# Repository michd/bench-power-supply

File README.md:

# Bench power supply

I'm working (currently just researching and prototyping) on developing my own bench power supply. This repository will mostly act as a working directory before it gets anywhere near completion, so expect stuff to move around a lot.

## Some requirements / desired features for the supply:

- DC output voltage of 1.5V - 35V (ish)
- Output current of up to 2.5~3A (ish)
- Voltage and current limit digitally adjustable, probably through rotary encoders
- Present output voltage and current displayed on LED 7 segment displays
- Additional (LCD?) display for setting the voltage and current limit (definitely need a way to view the current limit when it's not being reached)
- Maybe some USB ports (3?) providing 5V / 1A per port.

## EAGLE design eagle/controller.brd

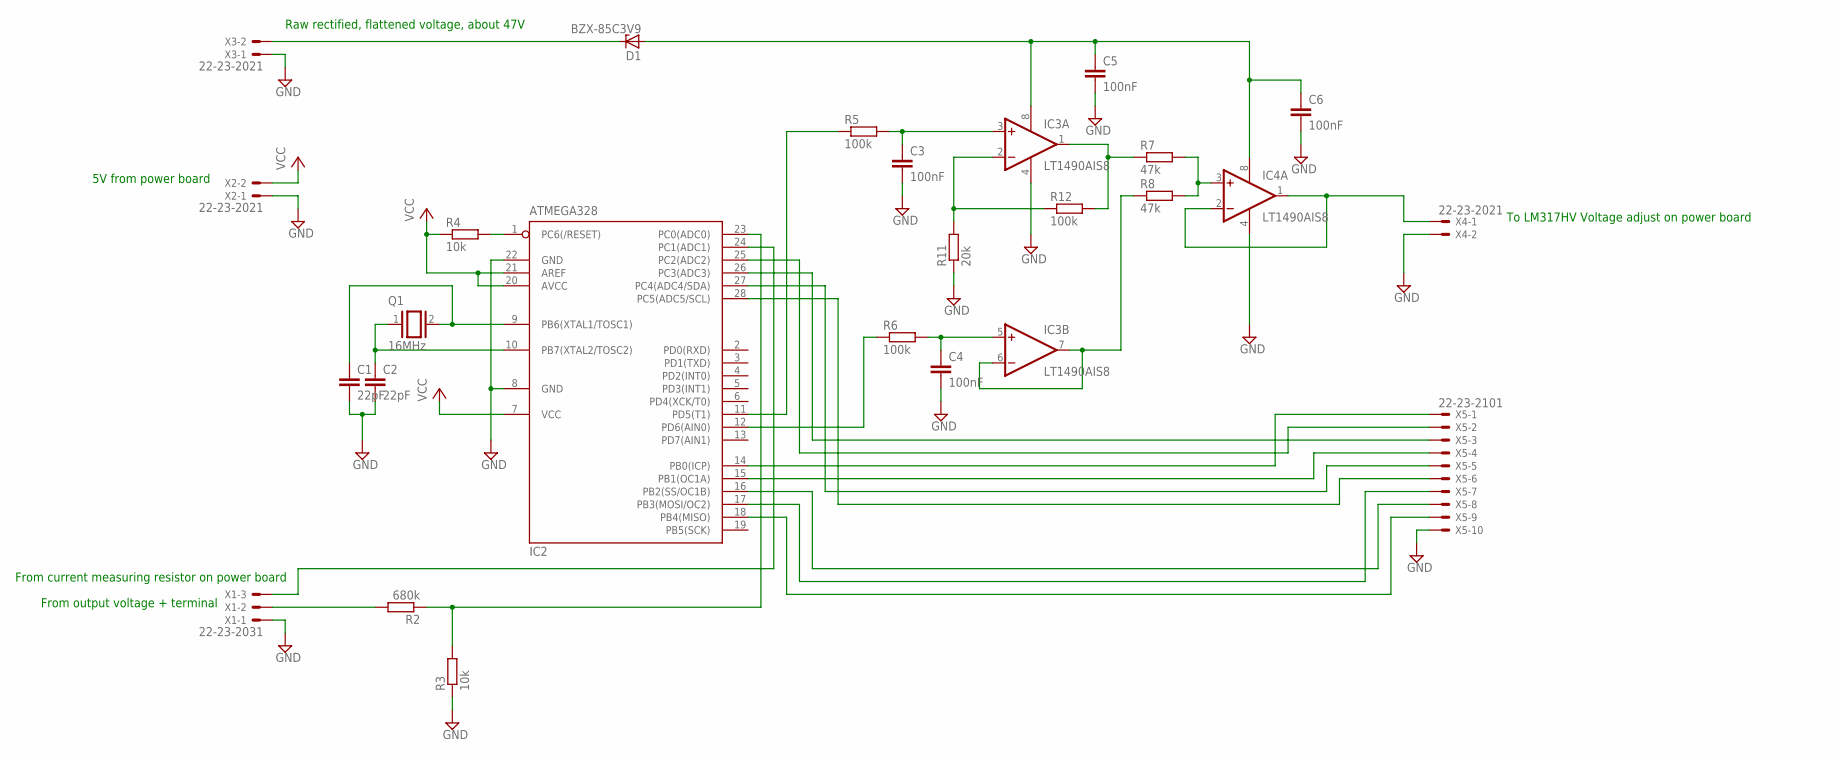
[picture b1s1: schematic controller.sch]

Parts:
C1, C2: 22pF; C2.5-2
C3, C4, C5, C6: 100nF; C7.5B3
D1: BZX-85C3V9; DO34Z7
IC2: ATMEGA328; DIL28-3
IC3, IC4: LT1490AIS8; SO08
Q1: 16MHz; QS
R2: 680k; 0207/10
R3, R4: 10k; 0207/10
R5, R6, R12: 100k; 0207/10
R7, R8: 47k; 0207/10
R11: 20k; 0207/10
X1: 22-23-2031
X2, X3, X4: 22-23-2021
X5: 22-23-2101

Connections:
GND: C1.2, C2.2, C3.2, C4.2, C5.2, C6.2, IC2.8 (GND), IC2.22 (GND), IC3.4 (V-), IC4.4 (V-), R3.1, R11.1, X1.1, X2.1, X3.1, X4.2, X5.10
unnamed: IC2.18 (PB4(MISO)), X5.9
unnamed: IC2.16 (PB2(SS/OC1B)), X5.8
unnamed: IC2.17 (PB3(MOSI/OC2)), X5.7
unnamed: IC2.7 (VCC), IC2.20 (AVCC), IC2.21 (AREF), R4.1, X2.2
unnamed: IC3.1 (OUT), R7.1, R12.2
unnamed: IC2.14 (PB0(ICP)), X5.1
unnamed: IC2.24 (PC1(ADC1)), X1.3
unnamed: IC2.23 (PC0(ADC0)), R2.1, R3.2
unnamed: R2.2, X1.2
unnamed: C1.1, IC2.9 (PB6(XTAL1/TOSC1)), Q1.2
unnamed: C2.1, IC2.10 (PB7(XTAL2/TOSC2)), Q1.1
unnamed: IC3.6 (-IN), IC3.7 (OUT), R8.1
unnamed: IC2.11 (PD5(T1)), R5.1
unnamed: IC2.1 (PC6(/RESET)), R4.2
unnamed: C3.1, IC3.3 (+IN), R5.2
unnamed: C4.1, IC3.5 (+IN), R6.2
unnamed: C5.1, C6.1, D1.A, IC3.8 (V+), IC4.8 (V+)
unnamed: IC2.12 (PD6(AIN0)), R6.1
unnamed: IC4.3 (+IN), R7.2, R8.2
unnamed: IC3.2 (-IN), R11.2, R12.1
unnamed: IC4.1 (OUT), IC4.2 (-IN), X4.1
unnamed: IC2.15 (PB1(OC1A)), X5.4
unnamed: IC2.25 (PC2(ADC2)), X5.2
unnamed: IC2.28 (PC5(ADC5/SCL)), X5.6
unnamed: IC2.27 (PC4(ADC4/SDA)), X5.5
unnamed: D1.C, X3.2
unnamed: IC2.26 (PC3(ADC3)), X5.3

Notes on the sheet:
5V from power board
Raw rectified, flattened voltage, about 47V
To LM317HV Voltage adjust on power board
From current measuring resistor on power board
From output voltage + terminal

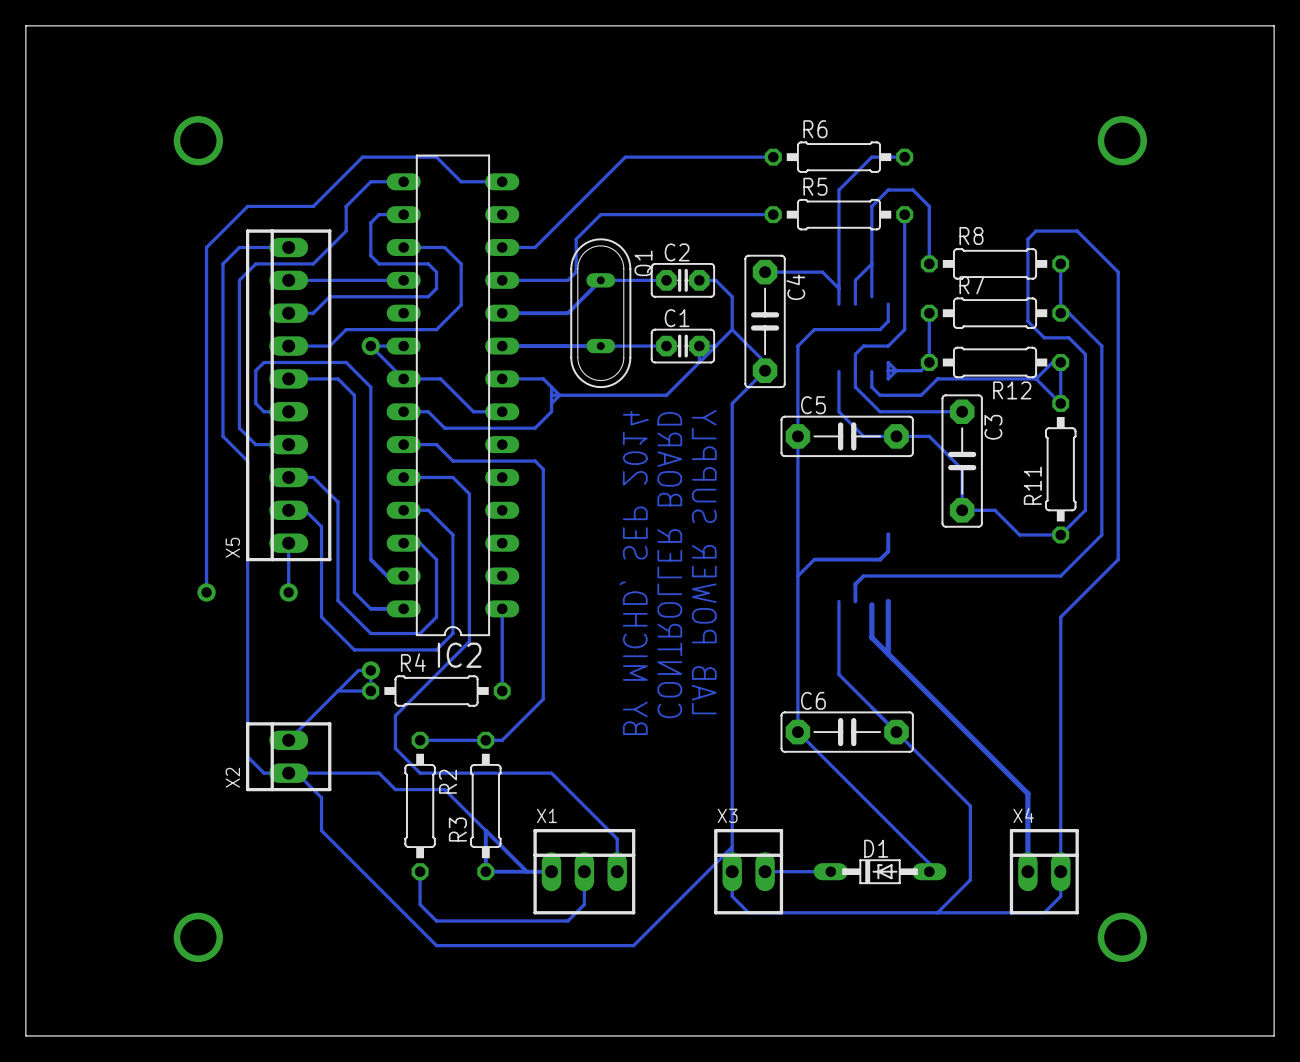
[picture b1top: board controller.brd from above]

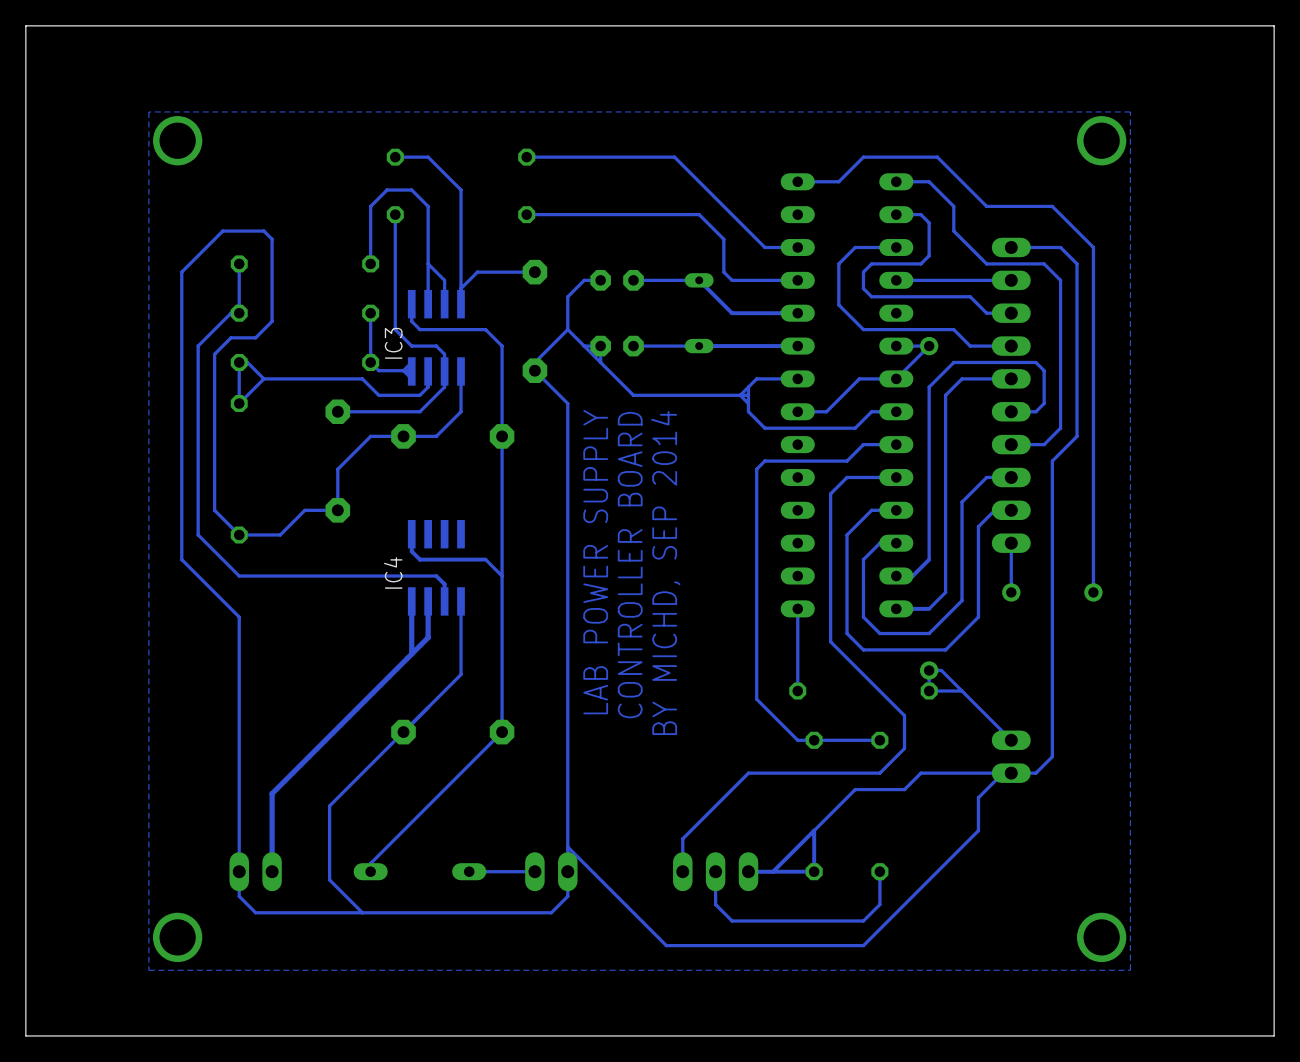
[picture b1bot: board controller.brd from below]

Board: 2 copper layers, 96.5 x 78.1 mm, 25 parts (2 on the bottom side), 28 nets.

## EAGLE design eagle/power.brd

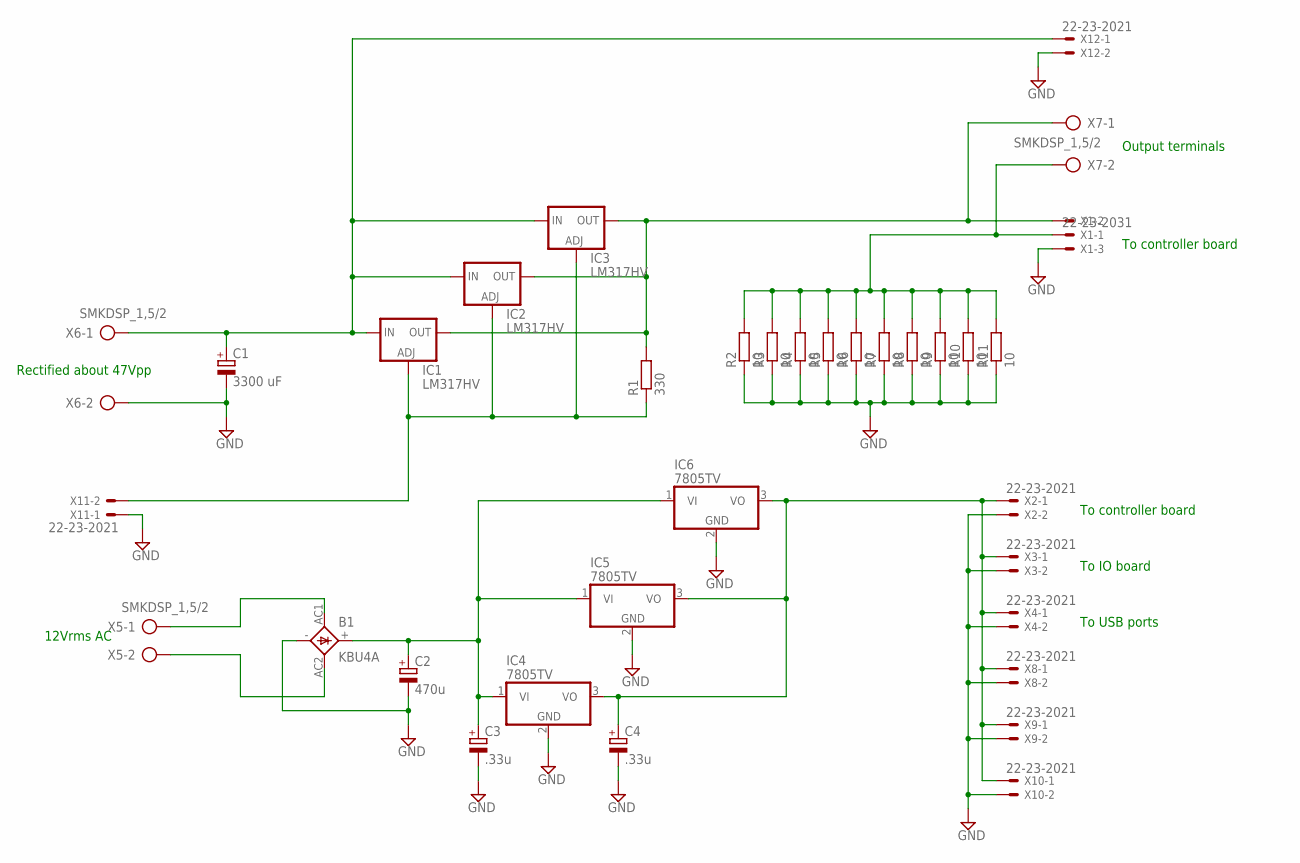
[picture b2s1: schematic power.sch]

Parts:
B1: KBU4A; 2KBB-R
C1: 3300 uF; EB25D
C2: 470u; E5-10,5
C3, C4: .33u; E2-5
IC1, IC2, IC3: LM317HV; 317TS
IC4, IC5, IC6: 7805TV; TO220V
R1: 330; 0207/7
R2, R3, R4, R5, R6, R7, R8, R9, R10, R11: 10; 0204/7
X1: 22-23-2031
X2, X3, X4, X8, X9, X10, X11, X12: 22-23-2021
X5, X6, X7: SMKDSP_1,5/2

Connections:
GND: B1.-, C1.-, C2.-, C3.-, C4.-, IC4.2 (GND), IC5.2 (GND), IC6.2 (GND), R2.1, R3.1, R4.1, R5.1, R6.1, R7.1, R8.1, R9.1, R10.1, R11.1, X1.3, X2.2, X3.2, X4.2, X6.2, X8.2, X9.2, X10.2, X11.1, X12.2
unnamed: B1.AC1, X5.1
unnamed: C1.+, IC1.3 (IN), IC2.3 (IN), IC3.3 (IN), X6.1, X12.1
unnamed: B1.AC2, X5.2
unnamed: IC1.2 (OUT), IC2.2 (OUT), IC3.2 (OUT), R1.2, X1.2, X7.1
unnamed: B1.+, C2.+, C3.+, IC4.1 (VI), IC5.1 (VI), IC6.1 (VI)
unnamed: C4.+, IC4.3 (VO), IC5.3 (VO), IC6.3 (VO), X2.1, X3.1, X4.1, X8.1, X9.1, X10.1
unnamed: IC1.1 (ADJ), IC2.1 (ADJ), IC3.1 (ADJ), R1.1, X11.2
unnamed: R2.2, R3.2, R4.2, R5.2, R6.2, R7.2, R8.2, R9.2, R10.2, R11.2, X1.1, X7.2

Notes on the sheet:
Rectified about 47Vpp
12Vrms AC
Output terminals
To controller board
To IO board
To USB ports

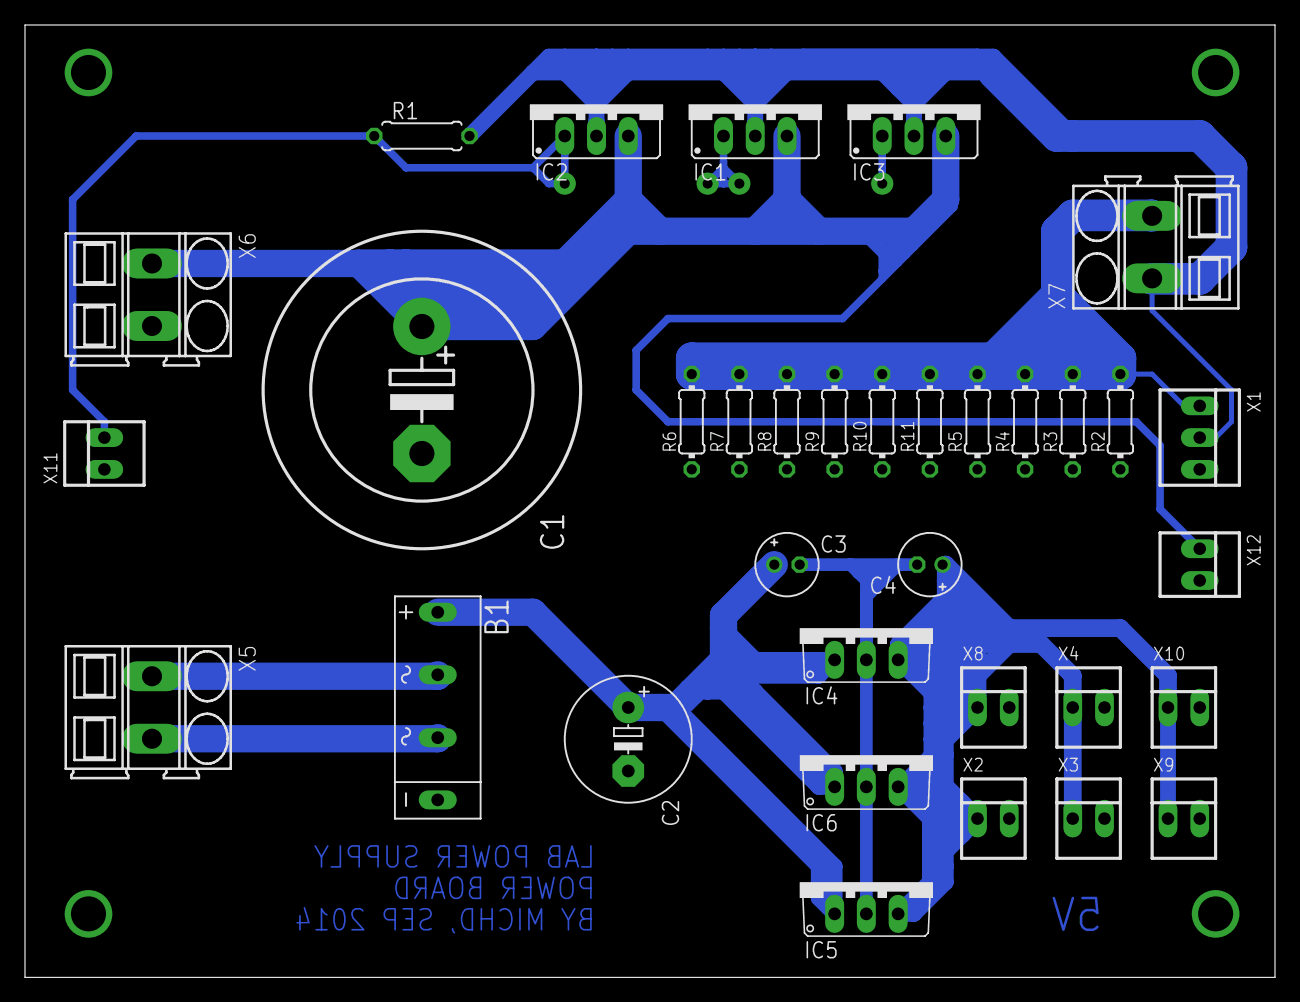
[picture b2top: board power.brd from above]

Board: 2 copper layers, 100.0 x 76.2 mm, 34 parts (0 on the bottom side), 9 nets.

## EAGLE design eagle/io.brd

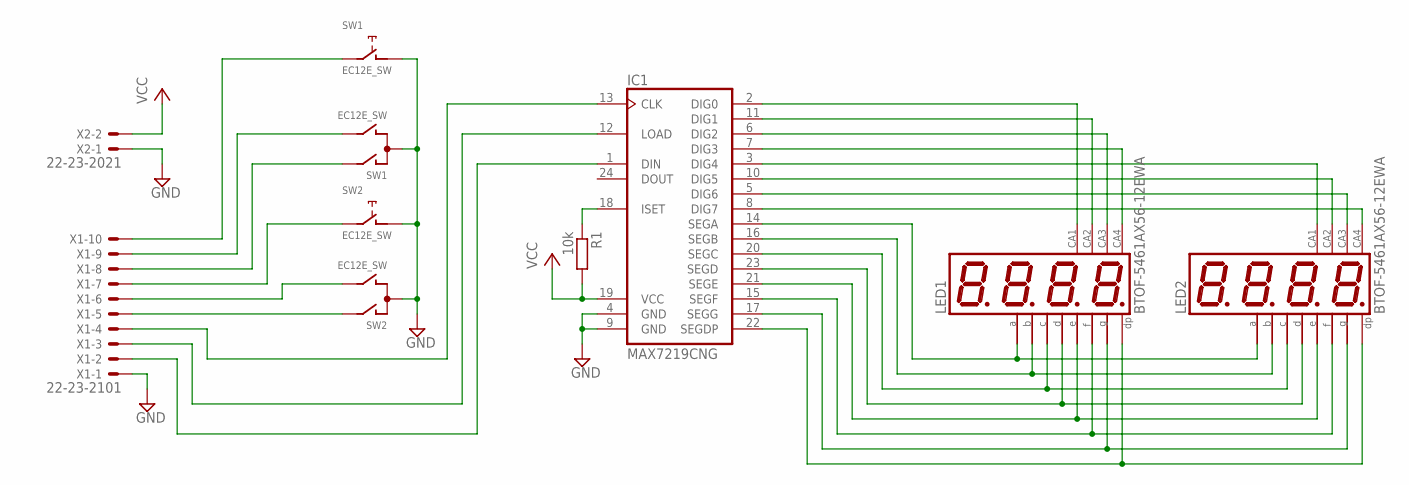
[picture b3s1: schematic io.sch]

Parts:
IC1: MAX7219CNG; DIL24-3
LED1, LED2: BTOF-5461AX56-12EWA; BX56-12
R1: 10k; 0207/10
SW1, SW2: EC12E_SW; ALPS_EC12E_SW
X1: 22-23-2101
X2: 22-23-2021

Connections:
GND: IC1.4 (GND), IC1.9 (GND), SW1.C, SW1.D (1), SW2.C, SW2.D (1), X1.1, X2.1
unnamed: IC1.12 (LOAD), X1.3
unnamed: IC1.2 (DIG0), LED1.12 (CA)
unnamed: IC1.11 (DIG1), LED1.9 (CA)
unnamed: IC1.6 (DIG2), LED1.8 (CA)
unnamed: IC1.3 (DIG4), LED2.12 (CA)
unnamed: IC1.5 (DIG6), LED2.8 (CA)
unnamed: IC1.8 (DIG7), LED2.6 (CA)
unnamed: IC1.16 (SEGB), LED1.7 (B), LED2.7 (B)
unnamed: IC1.20 (SEGC), LED1.4 (C), LED2.4 (C)
unnamed: IC1.23 (SEGD), LED1.2 (D), LED2.2 (D)
unnamed: IC1.21 (SEGE), LED1.1 (E), LED2.1 (E)
unnamed: IC1.15 (SEGF), LED1.10 (F), LED2.10 (F)
unnamed: IC1.13 (CLK), X1.4
unnamed: IC1.18 (ISET), R1.1
unnamed: IC1.17 (SEGG), LED1.5 (G), LED2.5 (G)
unnamed: IC1.22 (SEGDP), LED1.3 (DP), LED2.3 (DP)
unnamed: IC1.1 (DIN), X1.2
unnamed: IC1.14 (SEGA), LED1.11 (A), LED2.11 (A)
unnamed: IC1.10 (DIG5), LED2.9 (CA)
unnamed: SW2.E (2), X1.7
unnamed: SW1.E (2), X1.10
unnamed: SW1.B, X1.9
unnamed: SW2.A, X1.5
unnamed: SW2.B, X1.6
unnamed: SW1.A, X1.8
unnamed: IC1.7 (DIG3), LED1.6 (CA)
VCC: IC1.19 (VCC), R1.2, X2.2

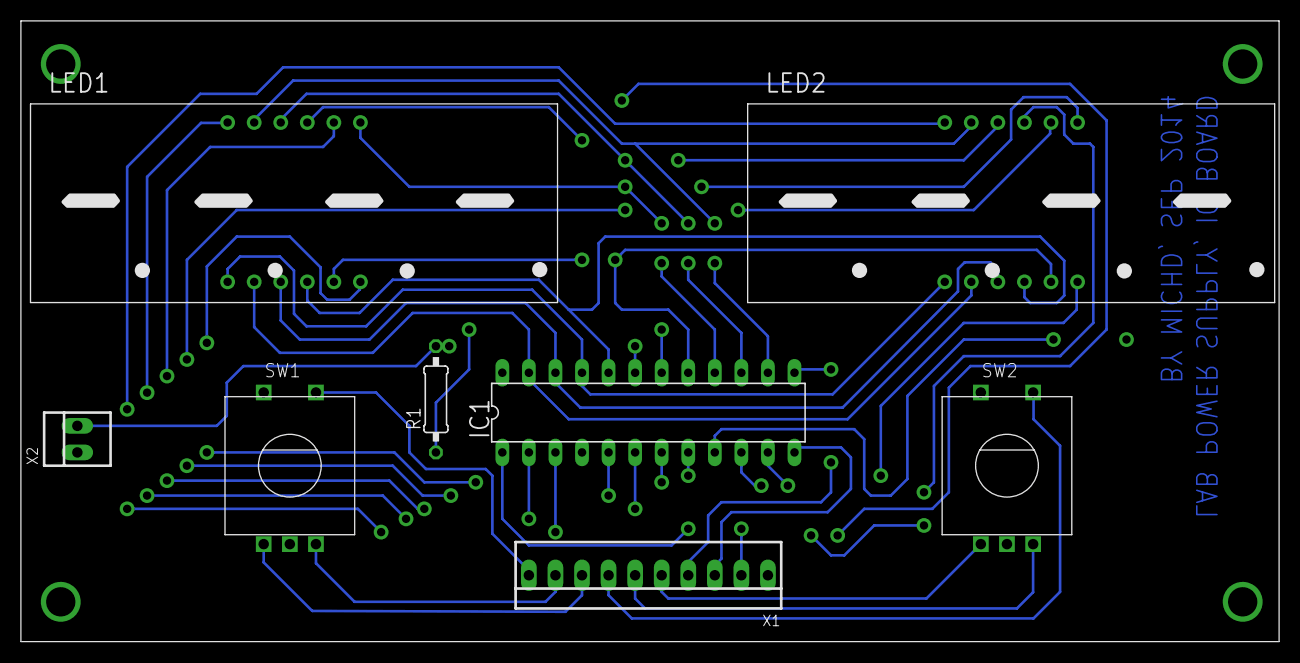
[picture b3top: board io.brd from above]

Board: 2 copper layers, 120.3 x 59.4 mm, 8 parts (0 on the bottom side), 28 nets.

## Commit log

2014-08-17 Add some info to the readme
2014-08-17 Add some arduino code for measuring voltage and current
2014-08-18 Add unfinished controller board schematic
2014-08-18 Add microcontroller to controller board schematic (still wip)
2014-08-19 More uC wiring + connector for controller schematic
2014-08-23 Added coarse/fine voltage regulation opamp circuit, moved things around Just needs rotary encoder/switches implemented
2014-08-23 Add some notes on rotary encoders/arduino after a session of experimenting
2014-08-24 Add a dual PWM precise voltage regulation arduino sketch
2014-08-24 Finished schematic
2014-08-24 Update 7 segment display digit mapping (arduino) in accordance with schematic
2014-08-24 Tweaks to controller schematic
    Note: controller board will be split into io schematic and controller
    schematic due to Eagle's free version board area constraints.
2014-08-24 Add io schematic, split off from controller schematic
2014-08-24 Remove IO parts from controller schematic and route to connector instead
2014-08-24 start a board layout for io board, needs routing
2014-08-24 Fix typo in readme
2014-09-07 Finish up controller board (including pcb)
2014-09-07 Route IO board (badly)
2014-09-14 Tighten up io board a bit, should be ready for etching
2014-09-14 add identifying text / credit on bottom layer of IO board
2014-09-20 Improve controller board design (Trace width, mounting holes, text)
2014-09-21 Add power board schematic
2014-09-22 Add power board pcb design
2014-09-26 Correct missing connector on power board `
2014-09-27 Fix up some polygon on power board
2014-10-06 Correct mistakes in the controller opamp circuit
    - Coarse voltage multiplier from 5->16.75V now from 5->30V
    - Summing opamp was doubling voltage, now just voltage follower
2014-10-06 Correct another mistake in controller board
2014-10-06 Start master psu controller code, map all the pins in defines
2014-10-06 Flesh out some structure for the arduino code
2014-10-07 Implement untested voltage and current reading
2014-10-08 Add screenshots of the PCB layouts in eagle
2014-10-10 Add partially tested voltage/current display implementation
2014-10-11 Measurement calibration, implement writeVoltage, tweak/fix display
2014-10-12 Implement all the things in arduino, untested.
    - Setting target voltage and current limit with rotary encoders
    - Adjusting output voltage according to targer voltage and taking into account
    current and current limit
    - Display modes for measurment and setting; when in setting, display
    will blink
    - Bunch of documenting
2014-10-12 Code style cleanup, tweaks to adjustOutputVoltage etc
2014-10-14 Tweaks and fixes during hardware testing
2014-10-18 Add bunch of measurements of boards and stuff
